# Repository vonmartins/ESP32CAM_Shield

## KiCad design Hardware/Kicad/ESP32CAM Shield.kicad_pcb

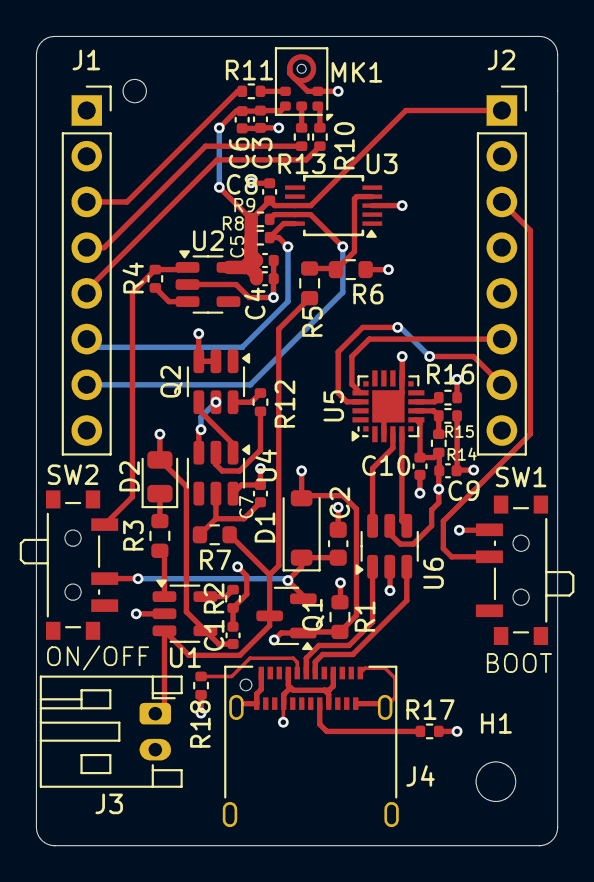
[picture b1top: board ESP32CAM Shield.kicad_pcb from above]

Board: 4 copper layers, 29.0 x 45.0 mm, 46 parts (0 on the bottom side), 35 nets.

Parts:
C1, C3, C7, C8, C10: 100n; C_0402_1005Metric
C2: 1u; C_0603_1608Metric
C4: 1u; C_0402_1005Metric
C5: 10u; C_0402_1005Metric
C6: 200p; C_0402_1005Metric
C9: 4.7u; C_0402_1005Metric
D1: D_Schottky_Small; D_SOD-123
D2: LED; LED_0805_2012Metric
H1: MountingHole; MountingHole_2.2mm_M2
J1, J2: Conn_01x08_Socket; PinSocket_1x08_P2.54mm_Vertical
J3: JST-PH; JST_PH_S2B-PH-K_1x02_P2.00mm_Horizontal
J4: USB_C_Receptacle_USB2.0_14P; USB_C_Receptacle_Amphenol_12401610E4-2A
MK1: SPH0645LM4H; Knowles_SPH0645LM4H-6_3.5x2.65mm
Q1: AO3401A; SOT-23
Q2: FS8205A; SOT-23-6
R1: 10k; R_0603_1608Metric
R2: 2k; R_0402_1005Metric
R3: 470; R_0603_1608Metric
R4: 100k; R_0402_1005Metric
R5, R6: 100k; R_0603_1608Metric
R7: 100; R_0603_1608Metric
R8, R9: 4.7k; R_0402_1005Metric
R10, R11, R13: 51; R_0402_1005Metric
R12, R16: 1k; R_0402_1005Metric
R14: 22k; R_0402_1005Metric
R15: 47k; R_0402_1005Metric
R17, R18: 5.1k; R_0402_1005Metric
SW1, SW2: SW_SPDT; SW_SPDT_PCM12
U1: MCP73831-2-OT; SOT-23-5
U2: AP2112K-3.3; SOT-23-5
U3: ADS1115IDGS; TSSOP-10_3x3mm_P0.5mm
U4: DW01A; SOT-23-6
U5: CP2102N-Axx-xQFN20; SiliconLabs_QFN-20-1EP_3x3mm_P0.5mm_EP1.8x1.8mm
U6: USBLC6-2SC6; SOT-23-6

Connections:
+3.3V: C3.1, C4.1, C5.1, C6.1, C8.1, J2.1, MK1.5 (VDD), R8.2, R9.2, U2.5 (VOUT), U3.8 (VDD)
+BATT: J3.1, Q1.3 (D), R5.2, R7.1, U1.3 (V_{BAT})
GND: C1.2, C2.2, C3.2, C4.2, C5.2, C6.2, C7.2, C8.2, C9.2, C10.2, J1.2, J2.4, J2.8, J3.2, J4.A1 (GND), J4.A12 (GND), J4.B1 (GND), J4.B12 (GND), J4.S1 (SHIELD), MK1.2 (SEL), MK1.3 (GND), Q2.2, Q2.3, R1.1, R2.1, R6.1, R15.2, R17.2, R18.2, SW1.3 (C), U1.2 (V_{SS}), U2.2 (GND), U3.3 (GND), U4.6 (GND), U5.3 (GND), U5.12 (GND), U5.21 (GND), U6.2 (GND)
I2C_SCL: J1.6, R8.1, U3.10 (SCL)
I2C_SDA: J1.7, R9.1, U3.9 (SDA)
I2S_BCLK: J1.3, R11.2
I2S_DATA: J1.4, R13.2
I2S_WS: J1.5, R10.2
unnamed: C2.1, D1.1 (K), Q1.2 (S), SW2.2 (B)
unnamed: D2.1 (K), R3.2
unnamed: J4.A5 (CC1), R18.1
unnamed: J4.B5 (CC2), R17.1
unnamed: MK1.4 (BCLK), R11.1
unnamed: MK1.6 (DATA), R13.1
unnamed: MK1.1 (WS), R10.1
unnamed: Q2.6, R12.2
unnamed: R4.2, SW2.1 (A), U2.1 (VIN)
unnamed: R2.2, U1.5 (PROG)
unnamed: R3.1, U1.1 (STAT)
unnamed: R4.1, U2.3 (EN)
unnamed: R5.1, R6.2, U3.4 (AIN0)
unnamed: R12.1, U4.2 (CS)
unnamed: Q2.5, U4.3 (OC)
unnamed: Q2.4, U4.1 (OD)
unnamed: C7.1, R7.2, U4.5 (VCC)
unnamed: R14.2, R15.1, U5.8 (VBUS)
unnamed: R16.2, U5.9 (~RST)
UART_USB_RX: J2.6, U5.17 (RXD)
UART_USB_TX: J2.7, U5.18 (TXD)
USB_CONN_D+: J4.A6 (D+), U6.1 (I/O1)
USB_CONN_D-: J4.A7 (D-), U6.3 (I/O2)
USB_D+: U5.4 (D+), U6.6 (I/O1)
USB_D-: U5.5 (D-), U6.4 (I/O2)
VBUS: C1.1, C9.1, C10.1, D1.2 (A), D2.2 (A), J4.A4 (VBUS), J4.A9 (VBUS), J4.B4 (VBUS), J4.B9 (VBUS), Q1.1 (G), R1.2, R14.1, R16.1, U1.4 (V_{DD}), U5.7 (VREGIN), U6.5 (VBUS)
io00: J2.3, SW1.2 (B)

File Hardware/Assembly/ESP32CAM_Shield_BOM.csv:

"Comment","Designator","Footprint","LCSC Part #"
"100n","C1","Capacitor_SMD:C_0402_1005Metric","C1525"
"1u","C2","Capacitor_SMD:C_0603_1608Metric","C15849"
"100n","C3","Capacitor_SMD:C_0402_1005Metric","C1525"
"1u","C4","Capacitor_SMD:C_0402_1005Metric","C52923"
"10u","C5","Capacitor_SMD:C_0402_1005Metric","C15525"
"220p","C6","Capacitor_SMD:C_0402_1005Metric","C1530"
"100n","C7","Capacitor_SMD:C_0402_1005Metric","C1525"
"100n","C8","Capacitor_SMD:C_0402_1005Metric","C1525"
"4.7u","C9","Capacitor_SMD:C_0402_1005Metric","C23733"
"100n","C10","Capacitor_SMD:C_0402_1005Metric","C1525"
"D_Schottky_Small","D1","Diode_SMD:D_SOD-123","C8598"
"LED","D2","LED_SMD:LED_0805_2012Metric","C34499"
"MountingHole","H1","MountingHole:MountingHole_2.2mm_M2",""
"Conn_01x08_Socket","J1","Connector_PinSocket_2.54mm:PinSocket_1x08_P2.54mm_Vertical","C27438"
"Conn_01x08_Socket","J2","Connector_PinSocket_2.54mm:PinSocket_1x08_P2.54mm_Vertical","C27438"
"JST-PH","J3","Connector_JST:JST_PH_S2B-PH-K_1x02_P2.00mm_Horizontal","C265016"
"USB_C_Receptacle_USB2.0_14P","J4","Connector_USB:USB_C_Receptacle_Amphenol_12401610E4-2A","C5119948"
"SPH0645LM4H","MK1","Sensor_Audio:Knowles_SPH0645LM4H-6_3.5x2.65mm","C19272537"
"AO3401A","Q1","Package_TO_SOT_SMD:SOT-23","C15127"
"FS8205A","Q2","Package_TO_SOT_SMD:SOT-23-6","C2830320"
"10k","R1","Resistor_SMD:R_0603_1608Metric","C25804"
"2k","R2","Resistor_SMD:R_0402_1005Metric","C4109"
"470","R3","Resistor_SMD:R_0603_1608Metric","C23179"
"100k","R4","Resistor_SMD:R_0402_1005Metric","C25741"
"100k","R5","Resistor_SMD:R_0603_1608Metric","C25803"
"100k","R6","Resistor_SMD:R_0603_1608Metric","C25803"
"100","R7","Resistor_SMD:R_0603_1608Metric","C22775"
"4.7k","R8","Resistor_SMD:R_0402_1005Metric","C25900"
"4.7k","R9","Resistor_SMD:R_0402_1005Metric","C25900"
"51","R10","Resistor_SMD:R_0402_1005Metric","C25125"
"51","R11","Resistor_SMD:R_0402_1005Metric","C25125"
"1k","R12","Resistor_SMD:R_0402_1005Metric","C11702"
"51","R13","Resistor_SMD:R_0402_1005Metric","C25125"
"22k","R14","Resistor_SMD:R_0402_1005Metric","C25768"
"47k","R15","Resistor_SMD:R_0402_1005Metric","C25792"
"1k","R16","Resistor_SMD:R_0402_1005Metric","C11702"
"5.1k","R17","Resistor_SMD:R_0402_1005Metric","C25905"
"5.1k","R18","Resistor_SMD:R_0402_1005Metric","C25905"
"SW_SPDT","SW1","Button_Switch_SMD:SW_SPDT_PCM12","C431541"
"SW_SPDT","SW2","Button_Switch_SMD:SW_SPDT_PCM12","C431541"
"MCP73831-2-OT","U1","Package_TO_SOT_SMD:SOT-23-5","C14879"
"AP2112K-3.3","U2","Package_TO_SOT_SMD:SOT-23-5","C23380830"
"ADS1115IDGS","U3","Package_SO:TSSOP-10_3x3mm_P0.5mm","C37593"
"DW01A","U4","Package_TO_SOT_SMD:SOT-23-6","C18164398"
"CP2102N-Axx-xQFN20","U5","Package_DFN_QFN:SiliconLabs_QFN-20-1EP_3x3mm_P0.5mm_EP1.8x1.8mm","C969913"
"USBLC6-2SC6","U6","Package_TO_SOT_SMD:SOT-23-6","C7519"

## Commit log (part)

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2025-05-12 Added BOOT and ON/OFF switches text
2026-06-11 Project backup
